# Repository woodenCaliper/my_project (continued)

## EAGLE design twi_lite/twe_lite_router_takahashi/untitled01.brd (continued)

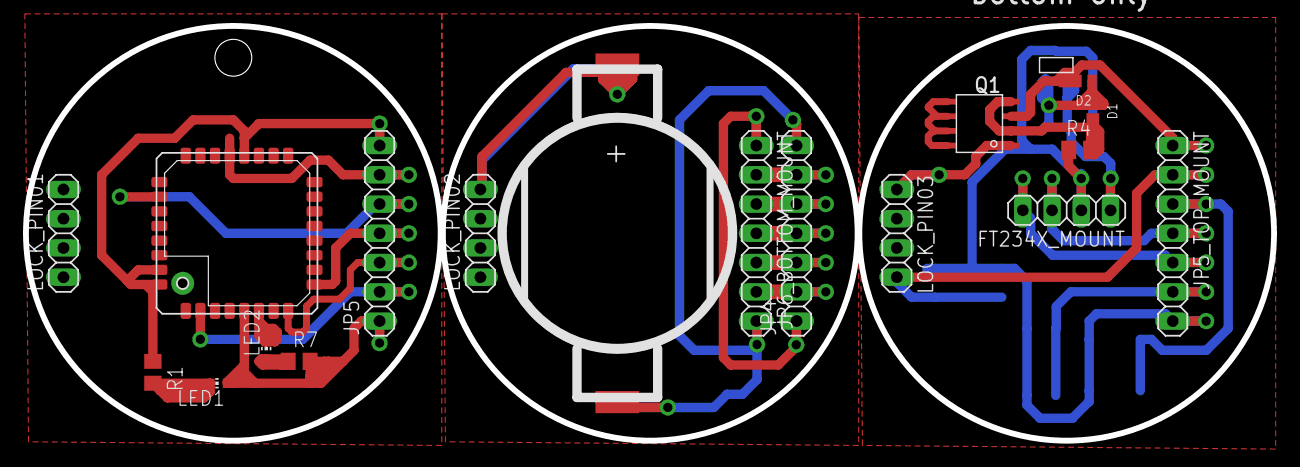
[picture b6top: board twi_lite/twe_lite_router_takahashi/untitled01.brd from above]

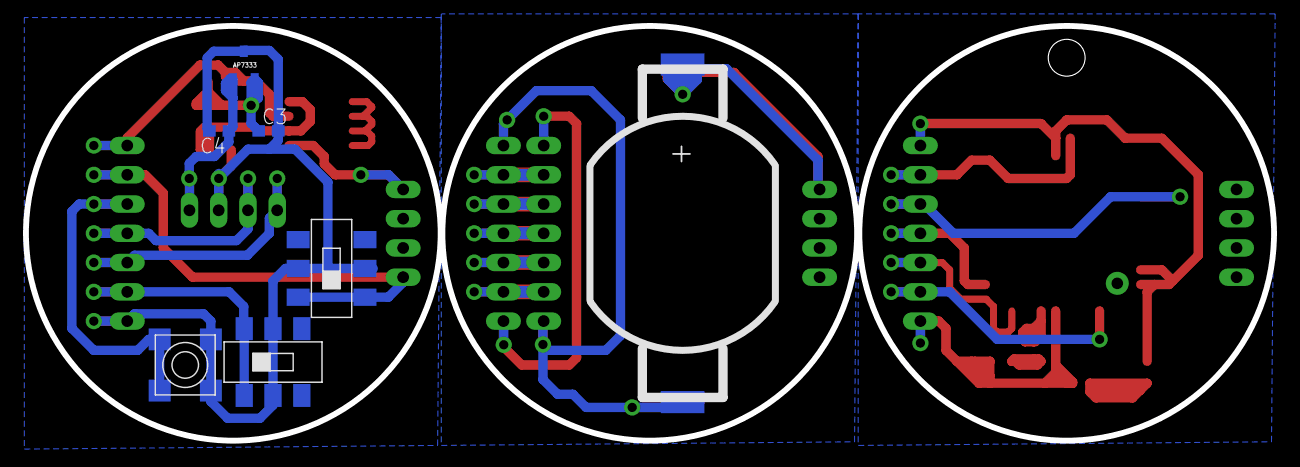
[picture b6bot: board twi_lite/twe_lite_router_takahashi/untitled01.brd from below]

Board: 2 copper layers, 108.3 x 36.0 mm, 25 parts (7 on the bottom side), 30 nets.

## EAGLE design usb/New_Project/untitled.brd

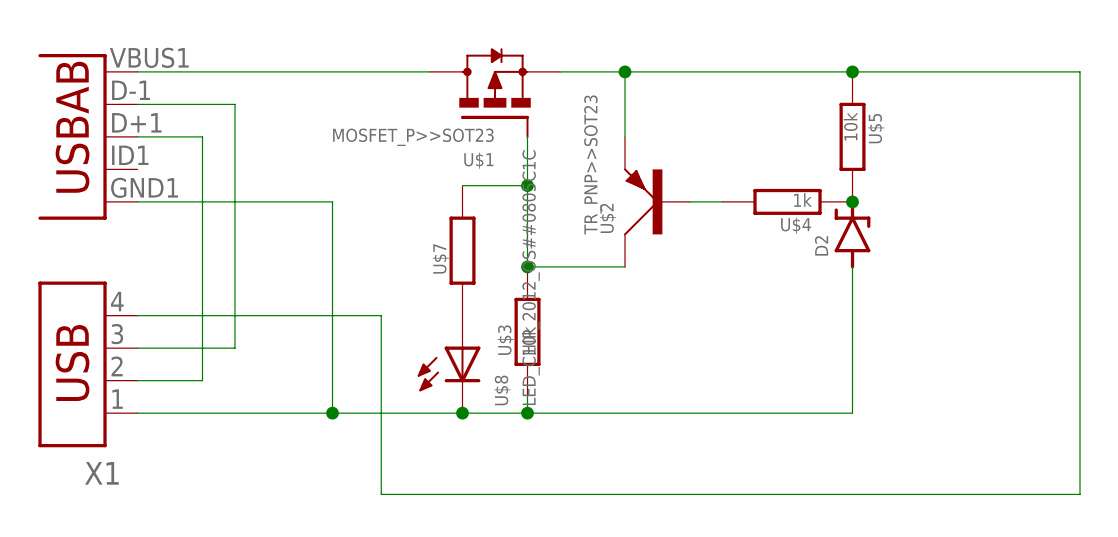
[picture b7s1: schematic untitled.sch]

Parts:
D2: ZENER-DIODE>>SOD-323; SOD323-W
U1: USB""; USB-MICRO-SMD
U$1: MOSFET_P>>SOT23; SOT23
U$2: TR_PNP>>SOT23; SOT23
U$3, U$5: 10k; 2012
U$4: 1k; 2012
U$7: REGISTER>>2012; 2012
U$8: LED_CHIP_2012_OS##0805C1C; 2012_OS##0805C1C
X1: USB-787616; USB

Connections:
unnamed: U1.D+1 (D+), X1.2
unnamed: U1.D-1 (D-), X1.3
unnamed: U$1.2 (S), U$2.2 (E), U$5.1, X1.4
unnamed: U1.VBUS1 (VBUS), U$1.3 (D)
unnamed: U$1.1 (G), U$2.3 (C), U$3.2, U$7.2
unnamed: U$2.1 (B), U$4.2
unnamed: D2.C, U$4.1, U$5.2
unnamed: U$7.1, U$8.P$1 (A)
unnamed: D2.A, U1.GND1 (GND), U$3.1, U$8.P$2 (C), X1.1

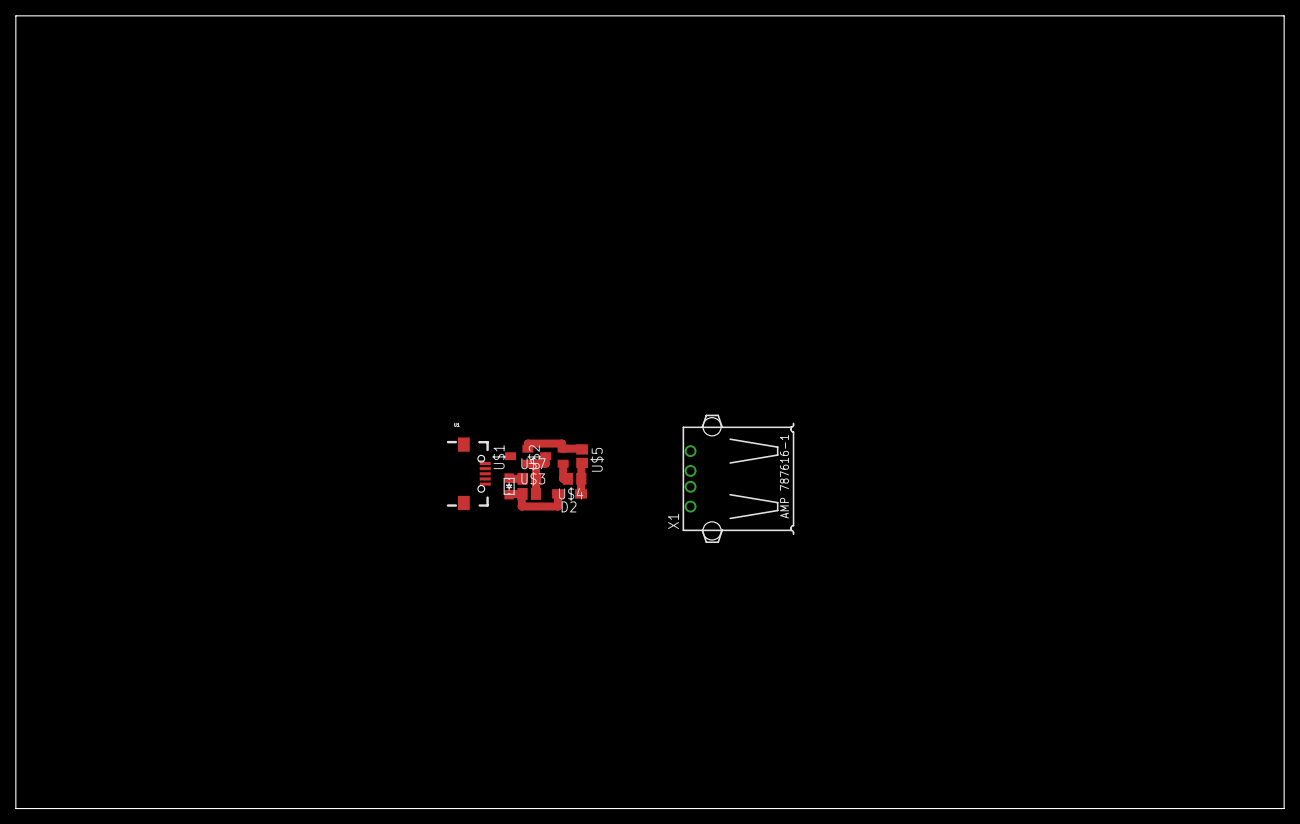
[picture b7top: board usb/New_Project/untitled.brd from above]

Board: 2 copper layers, 160.0 x 100.0 mm, 10 parts (0 on the bottom side), 9 nets.
